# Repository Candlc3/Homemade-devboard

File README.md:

# Homemade-devboard
homeade devboard with a screen and everything!
no firmware yet because i will work on that in a future project but it looks pretty good!

the entire idea is to have a decently powerful microcontroller (rp2350a) over an rp2040. i will def use this for a future project where i code the actual firmware. but for nowm it is a decently designed project that im glad i commited. It has all the basic requirements for a devboard, and it even connects to this screen im getting off amazon as well! the wiring was stupid hard, but i managed to make it all work.

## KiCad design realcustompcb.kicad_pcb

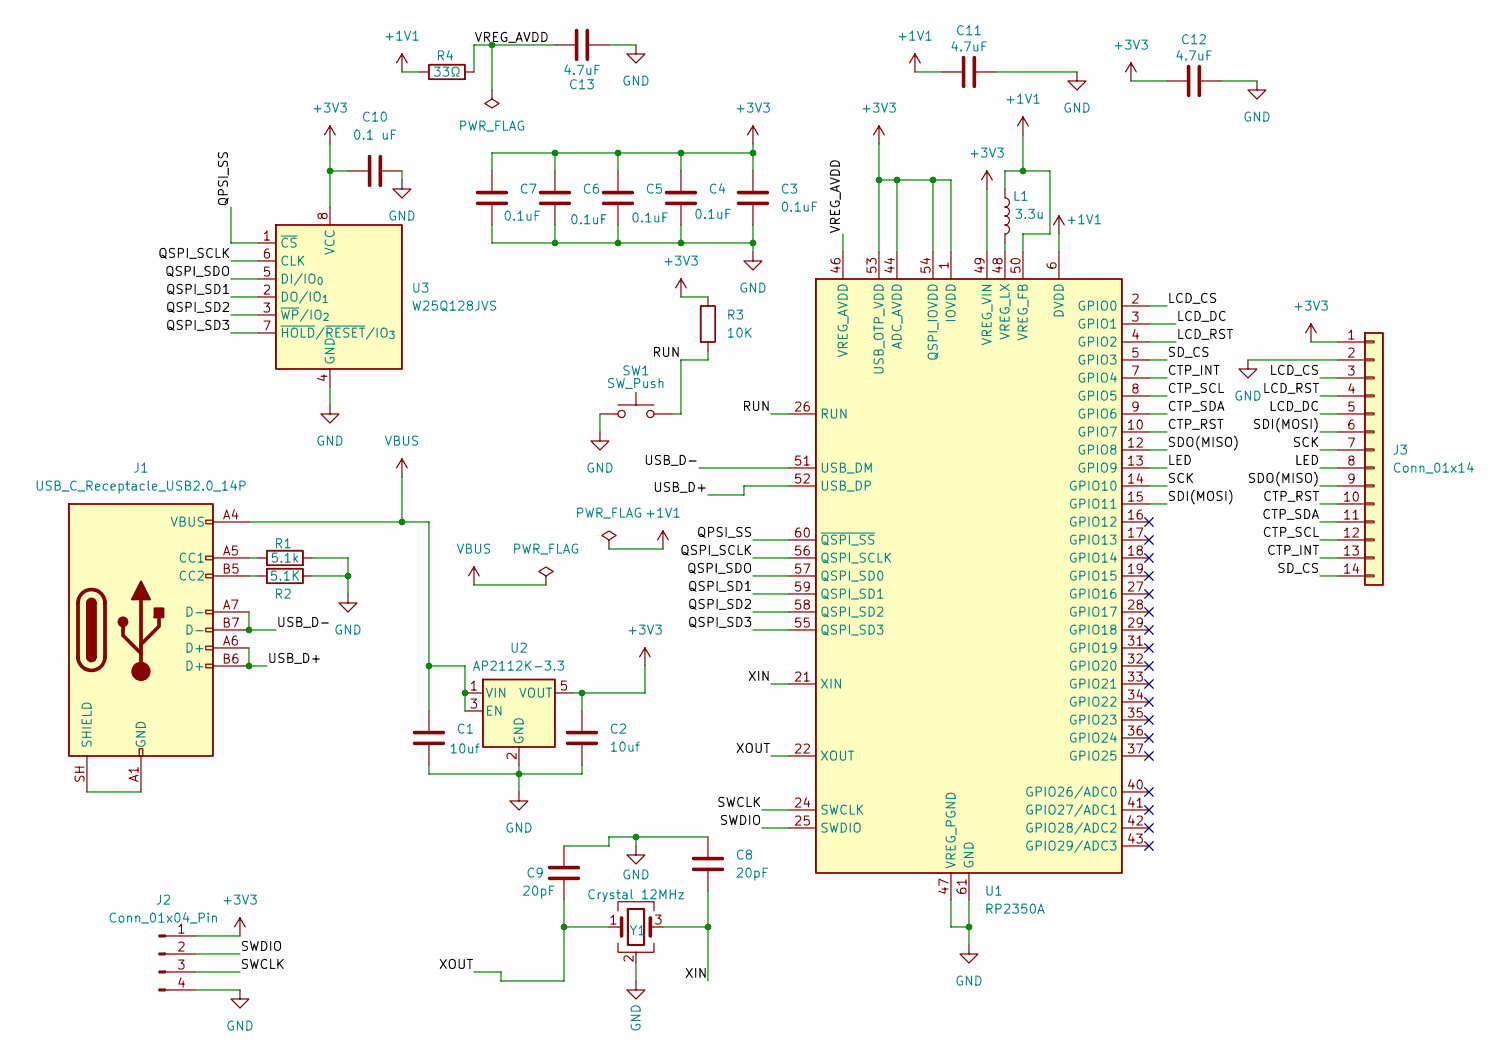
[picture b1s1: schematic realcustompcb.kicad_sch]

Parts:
C1, C2: 10uf; C_0603_1608Metric_Pad1.08x0.95mm_HandSolder
C3, C4, C5, C6, C7: 0.1uF; C_0603_1608Metric_Pad1.08x0.95mm_HandSolder
C8, C9: 20pF; C_0603_1608Metric_Pad1.08x0.95mm_HandSolder
C10: 0.1 uF; C_0603_1608Metric_Pad1.08x0.95mm_HandSolder
C11, C12, C13: 4.7uF; C_0603_1608Metric_Pad1.08x0.95mm_HandSolder
J1: USB_C_Receptacle_USB2.0_14P; USB_C_Receptacle_HRO_TYPE-C-31-M-12
J2: Conn_01x04_Pin; PinHeader_1x04_P2.54mm_Vertical
J3: Conn_01x14; PinHeader_1x14_P2.54mm_Vertical
L1: 3.3u; L_Sunlord_SWPA4030S
R1: 5.1k; R_0603_1608Metric_Pad0.98x0.95mm_HandSolder
R2: 5.1K; R_0603_1608Metric_Pad0.98x0.95mm_HandSolder
R3: 10K; R_0603_1608Metric_Pad0.98x0.95mm_HandSolder
R4: 33Ω; R_0603_1608Metric_Pad0.98x0.95mm_HandSolder
SW1: SW_Push; SW_SPST_TS-1088-xR020
U1: RP2350A; QFN-60-1EP_7x7mm_P0.4mm_EP3.4x3.4mm
U2: AP2112K-3.3; SOT-23-5
U3: W25Q128JVS; SOIC-8_5.3x5.3mm_P1.27mm
Y1: Crystal 12MHz; Crystal_SMD_3225-4Pin_3.2x2.5mm

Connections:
+1V1: C11.1, L1.1, R4.1, U1.6 (DVDD), U1.23 (DVDD), U1.39 (DVDD), U1.50 (VREG_FB)
+3V3: C2.1, C3.1, C4.1, C5.1, C6.1, C7.1, C10.1, C12.1, J2.1, J3.1, R3.1, U1.1 (IOVDD), U1.11 (IOVDD), U1.20 (IOVDD), U1.30 (IOVDD), U1.38 (IOVDD), U1.44 (ADC_AVDD), U1.45 (IOVDD), U1.49 (VREG_VIN), U1.53 (USB_OTP_VDD), U1.54 (QSPI_IOVDD), U2.5 (VOUT), U3.8 (VCC)
/CTP_INT: J3.13, U1.7 (GPIO4)
/CTP_RST: J3.10, U1.10 (GPIO7)
/CTP_SCL: J3.12, U1.8 (GPIO5)
/CTP_SDA: J3.11, U1.9 (GPIO6)
/LCD_CS: J3.3, U1.2 (GPIO0)
/LCD_DC: J3.5, U1.3 (GPIO1)
/LCD_RST: J3.4, U1.4 (GPIO2)
/LED: J3.8, U1.13 (GPIO9)
/QPSI_SS: U1.60 (~QSPI_SS), U3.1 (~CS)
/QSPI_SCLK: U1.56 (QSPI_SCLK), U3.6 (CLK)
/QSPI_SD1: U1.59 (QSPI_SD1), U3.2 (DO/IO_{1})
/QSPI_SD2: U1.58 (QSPI_SD2), U3.3 (~WP/IO_{2})
/QSPI_SD3: U1.55 (QSPI_SD3), U3.7 (~HOLD/~RESET/IO_{3})
/QSPI_SDO: U1.57 (QSPI_SD0), U3.5 (DI/IO_{0})
/RUN: R3.2, SW1.2, U1.26 (RUN)
/SCK: J3.7, U1.14 (GPIO10)
/SDI(MOSI): J3.6, U1.15 (GPIO11)
/SDO(MISO): J3.9, U1.12 (GPIO8)
/SD_CS: J3.14, U1.5 (GPIO3)
/SWCLK: J2.3, U1.24 (SWCLK)
/SWDIO: J2.2, U1.25 (SWDIO)
/USB_D+: J1.A6 (D+), J1.B6 (D+), U1.52 (USB_DP)
/USB_D-: J1.A7 (D-), J1.B7 (D-), U1.51 (USB_DM)
/VREG_AVDD: C13.1, R4.2, U1.46 (VREG_AVDD)
/XIN: C8.1, U1.21 (XIN), Y1.3
/XOUT: C9.2, U1.22 (XOUT), Y1.1
GND: C1.2, C2.2, C3.2, C4.2, C5.2, C6.2, C7.2, C8.2, C9.1, C10.2, C11.2, C12.2, C13.2, J2.4, J3.2, R1.2, R2.1, SW1.1, U1.47 (VREG_PGND), U1.61 (GND), U2.2 (GND), U3.4 (GND), Y1.2 (G), Y1.4 (G)
unnamed: J1.A5 (CC1), R1.1
unnamed: J1.B5 (CC2), R2.2
unnamed: J1.A1 (GND), J1.A12 (GND), J1.B1 (GND), J1.B12 (GND), J1.SH (SHIELD)
unnamed: L1.2, U1.48 (VREG_LX)
VBUS: C1.1, J1.A4 (VBUS), J1.A9 (VBUS), J1.B4 (VBUS), J1.B9 (VBUS), U2.1 (VIN), U2.3 (EN)

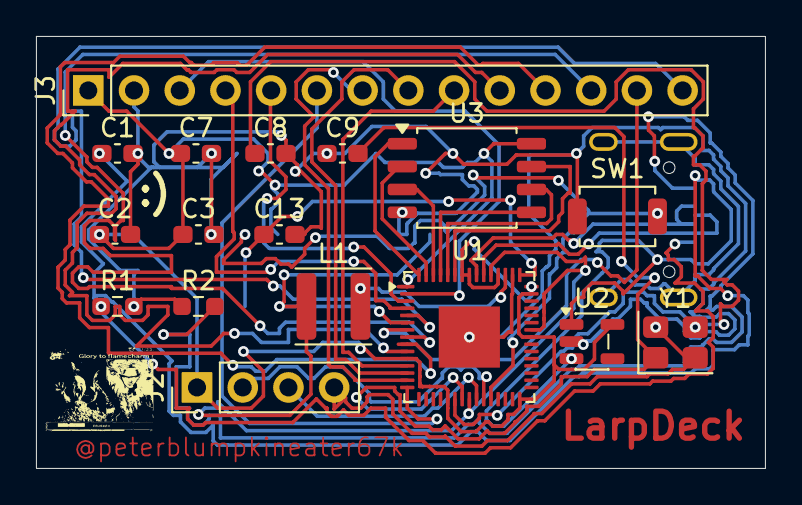
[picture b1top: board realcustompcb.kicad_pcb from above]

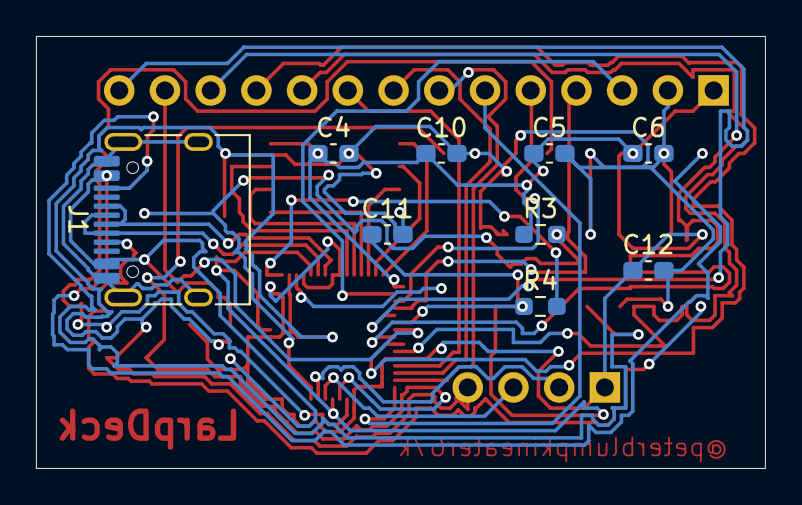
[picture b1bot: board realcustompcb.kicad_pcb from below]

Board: 2 copper layers, 40.5 x 24.0 mm, 26 parts (9 on the bottom side), 34 nets.
